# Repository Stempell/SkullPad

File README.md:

# SkullPad
Im buliding this macropad for Hack Club's stardance program! I'll be using it for shortcuts and volume controll.
Here's how it looks:

## Pcb schematic:

## Footprint:

The Pcb is rectangle with dimentions 61,65mm x 60,60mm

## 3D view:

## Case:

the case dimensions are 76,7mm x 75,6mm, excluding the corner chamferings

## Used libraries:
Joe Scotto's ScottoKicad - https://github.com/joe-scotto/scottokeebs/tree/main/Extras/ScottoKicad

Hack Club's KiCAD care package - https://github.com/hackclub/hackpad/releases/tag/v0.1-bugfix

## Bill OF Materials:
  
  1x xiao RP2040
  
  6x mx-style switches
  
  6x black keycaps
  
  6x through-hole 1N4148 diodes
  
  1x EC11 rotary encoder
  
  4x M3x16mm screws
  
  4x M3x5mx4mm heatset inserts
  
  1x 0.91 inch OLED display
  
  1x printed 61,7 x 60,6 circut board
  
  1x 3d printed case shell
  
  1x 3d printed case bottom plate

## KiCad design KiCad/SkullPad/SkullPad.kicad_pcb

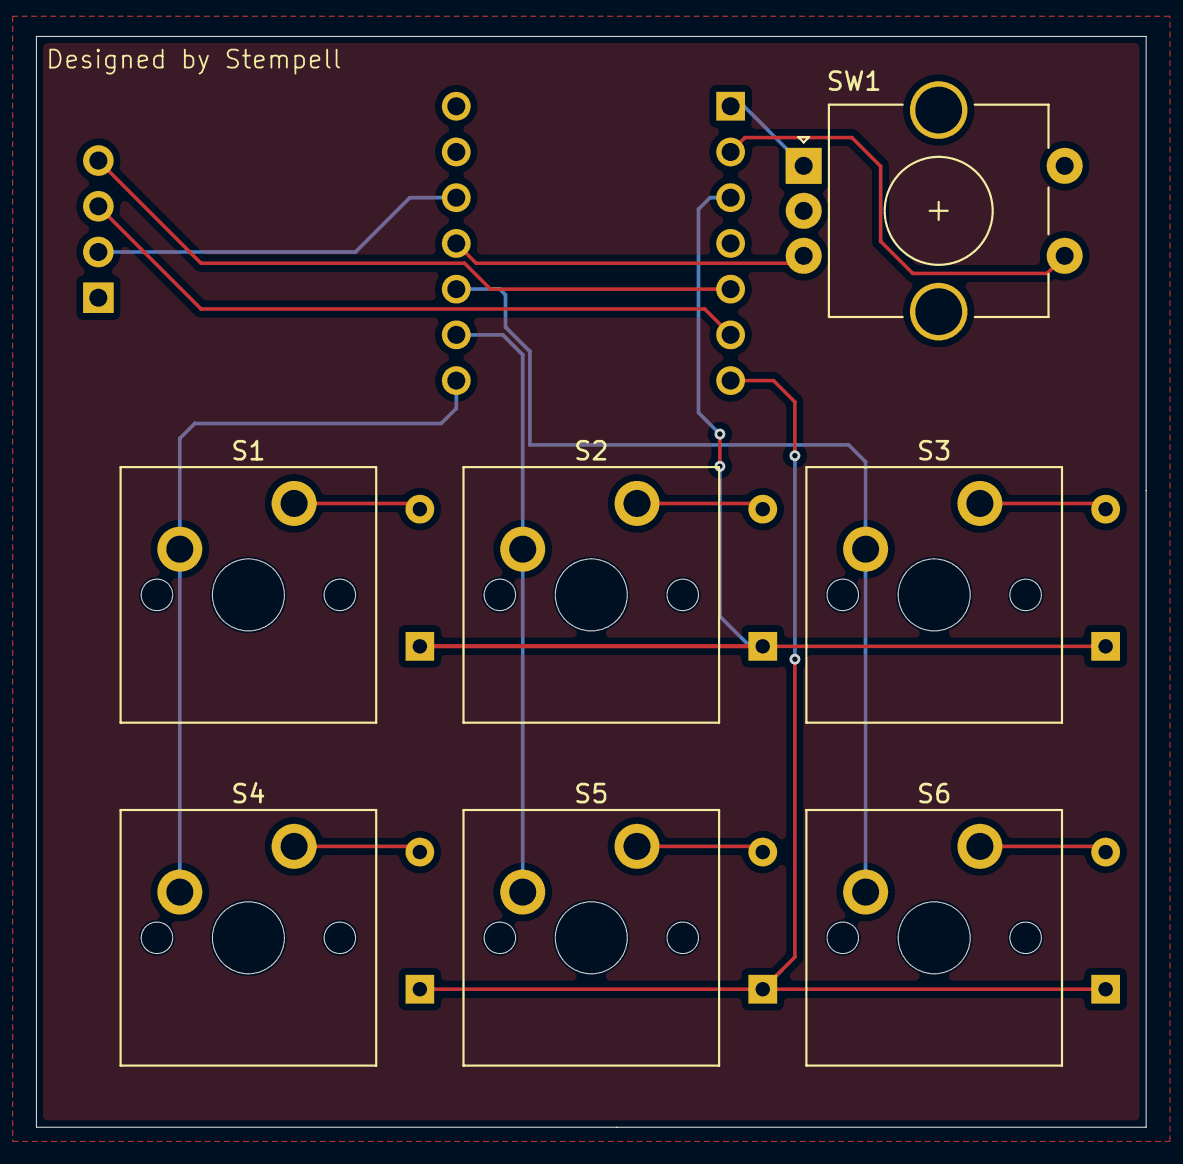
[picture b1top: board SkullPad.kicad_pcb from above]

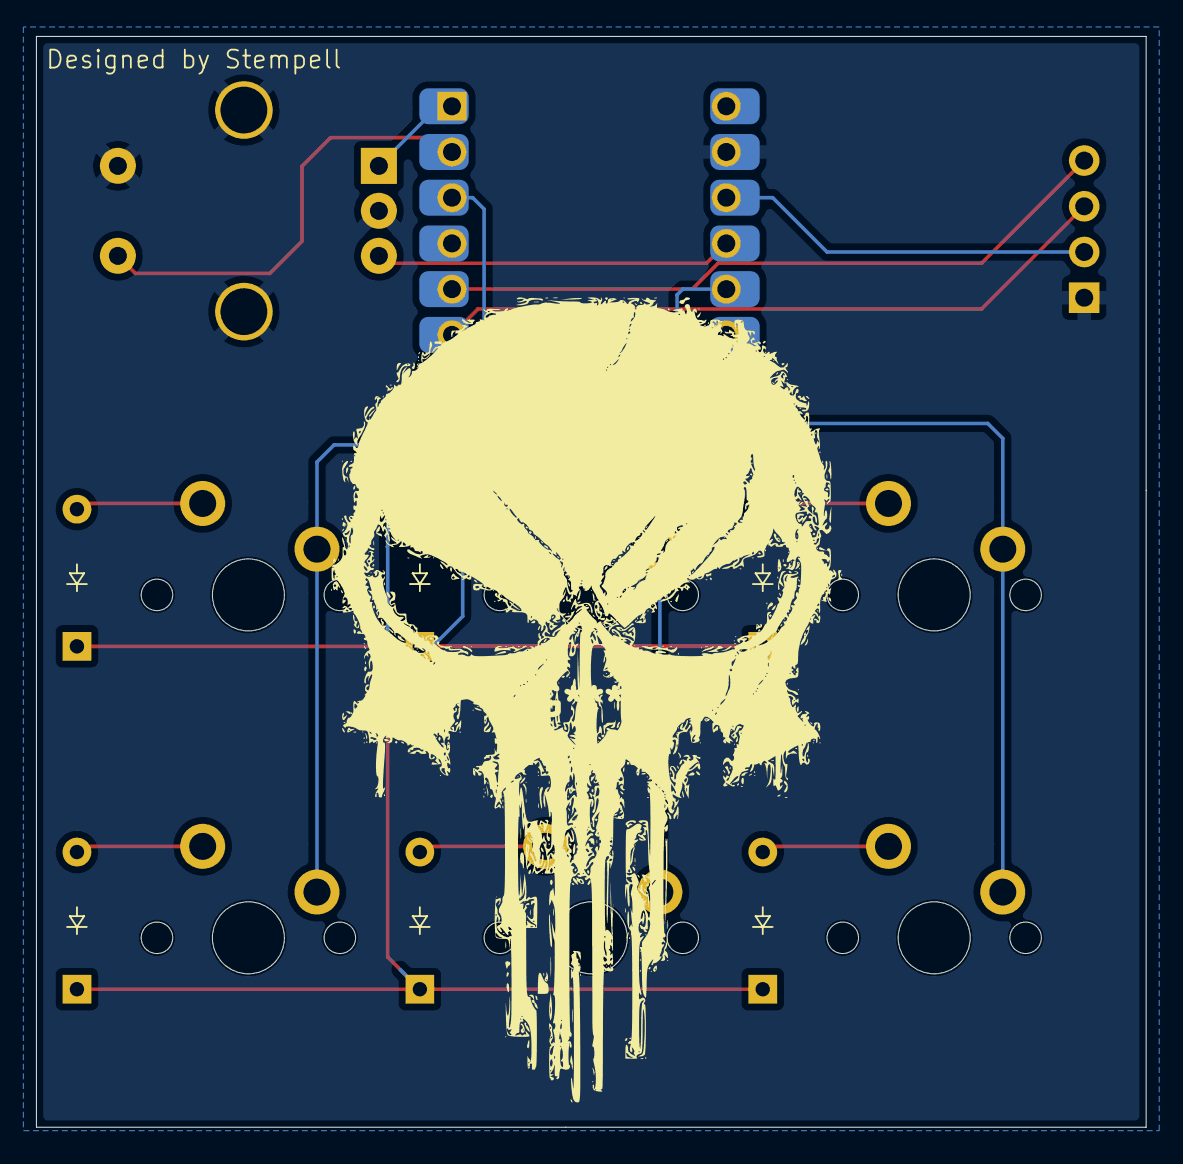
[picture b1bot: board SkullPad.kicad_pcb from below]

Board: 2 copper layers, 61.6 x 60.6 mm, 15 parts (7 on the bottom side), 18 nets.

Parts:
D1, D2, D3, D4, D5, D6: Diode_DO-35
J2: OLED_128x32
S1, S2, S3, S4, S5, S6: MX_PCB_1.00u
SW1: RotaryEncoder_Switch_MP; RotaryEncoder_Alps_EC11E-Switch_Vertical_H20mm_CircularMoun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
U1: XIAO-RP2040-DIP; Seeed_XIAO_RP2040

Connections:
CLK: SW1.A, U1.1 (P26_A0_D0)
Collumn_1: S1.1, S4.1, U1.8 (P1_D7_RX)
Collumn_2: S2.1, S5.1, U1.9 (P2_D8_SCK)
Collumn_3: S3.1, S6.1, U1.10 (P4_D9_MISO)
DT: SW1.B, U1.11 (P3_D10_MOSI)
GND: J2.1 (GND), SW1.C, SW1.MP, SW1.S2, U1.13 (GND)
unnamed: D1.2 (A), S1.2
unnamed: D2.2 (A), S2.2
unnamed: D3.2 (A), S3.2
unnamed: D4.2 (A), S4.2
unnamed: D5.2 (A), S5.2
unnamed: D6.2 (A), S6.2
Row_1: D1.1 (K), D2.1 (K), D3.1 (K), U1.3 (P28_A2_D2)
Row_2: D4.1 (K), D5.1 (K), D6.1 (K), U1.7 (P0_D6_TX)
SCL: J2.3 (SCL), U1.6 (P7_SCL_D5)
SDA: J2.4 (SDA), U1.5 (P6_SDA_D4)
VCC: J2.2 (VCC), U1.12 (3V3)
switch: SW1.S1, U1.2 (P27_A1_D1)

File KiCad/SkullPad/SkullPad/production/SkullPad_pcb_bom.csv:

Designator,Footprint,Quantity,Value,LCSC Part #
"D1, D2, D3, D4, D5, D6",Diode_DO-35,6,~,
J2,OLED_128x32,1,OLED_128x32,
"S1, S2, S3, S4, S5, S6",MX_PCB_1.00u,6,~,
SW1,RotaryEncoder_Alps_EC11E-Switch_Vertical_H20mm_CircularMountingHoles,1,RotaryEncoder_Switch_MP,
U1,Seeed_XIAO_RP2040,1,XIAO-RP2040-DIP,

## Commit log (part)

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2026-06-20 Create temp
2026-06-20 added photos of the pcb
2026-06-29 Update README.md
    redme update
2026-06-29 added bill of materials
2026-06-29 added .STEP's and gerbers
2026-06-29 Modified STEP's
2026-06-29 Replace images in README.md
    Updated images in the Footprint and 3D view sections.
